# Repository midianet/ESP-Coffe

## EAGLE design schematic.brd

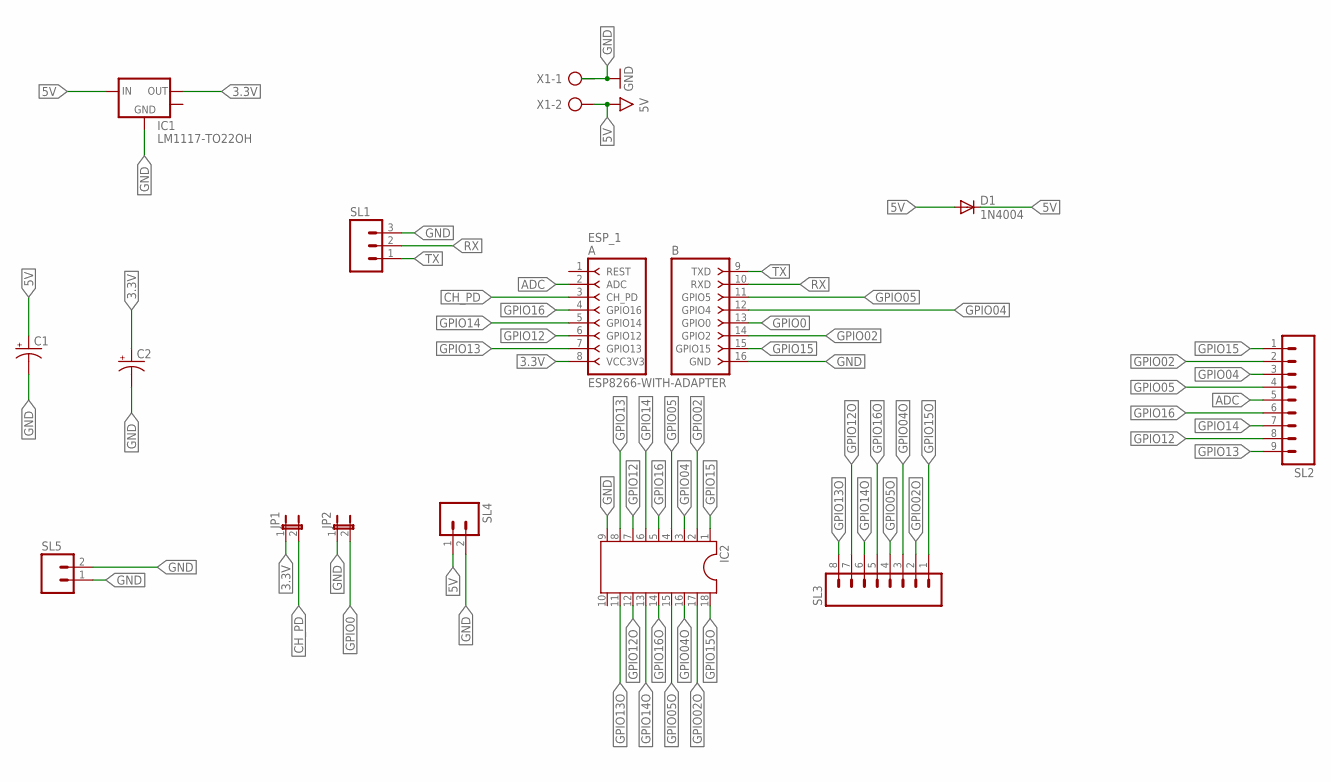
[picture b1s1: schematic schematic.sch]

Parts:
C1, C2: CPOL-USE2-4; E2-4
D1: 1N4004; DO41-10
ESP_1: ESP8266-WITH-ADAPTER; ESP8266-ADAPTER
IC1: LM1117-TO22OH; TO220L1
IC2: DIL18
JP1, JP2: JP1E; JP1
SL1: M03; 03P
SL2: M09; 09P
SL3: M08; 08P
SL4, SL5: M02; 02P
X1: AK500/2-H

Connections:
3.3V: C2.+, ESP_1.8 (VCC3V3), IC1.2 (VOUT), JP1.1
5V: C1.+, D1.A, D1.C, IC1.3 (VIN), SL4.1, X1.2
ADC: ESP_1.2 (ADC), SL2.5
CH_PD: ESP_1.3 (CH_PD), JP1.2
GND: C1.-, C2.-, ESP_1.16 (GND), IC1.1 (GND), IC2.9, JP2.1, SL1.3, SL4.2, SL5.1, SL5.2, X1.1
GPIO0: ESP_1.13 (GPIO0), JP2.2
GPIO02: ESP_1.14 (GPIO2), IC2.2, SL2.2
GPIO02O: IC2.17, SL3.2
GPIO04: ESP_1.12 (GPIO4), IC2.3, SL2.3
GPIO04O: IC2.16, SL3.3
GPIO05: ESP_1.11 (GPIO5), IC2.4, SL2.4
GPIO05O: IC2.15, SL3.4
GPIO12: ESP_1.6 (GPIO12), IC2.7, SL2.8
GPIO12O: IC2.12, SL3.7
GPIO13: ESP_1.7 (GPIO13), IC2.8, SL2.9
GPIO13O: IC2.11, SL3.8
GPIO14: ESP_1.5 (GPIO14), IC2.6, SL2.7
GPIO14O: IC2.13, SL3.6
GPIO15: ESP_1.15 (GPIO15), IC2.1, SL2.1
GPIO15O: IC2.18, SL3.1
GPIO16: ESP_1.4 (GPIO16), IC2.5, SL2.6
GPIO16O: IC2.14, SL3.5
RX: ESP_1.10 (RXD), SL1.2
TX: ESP_1.9 (TXD), SL1.1

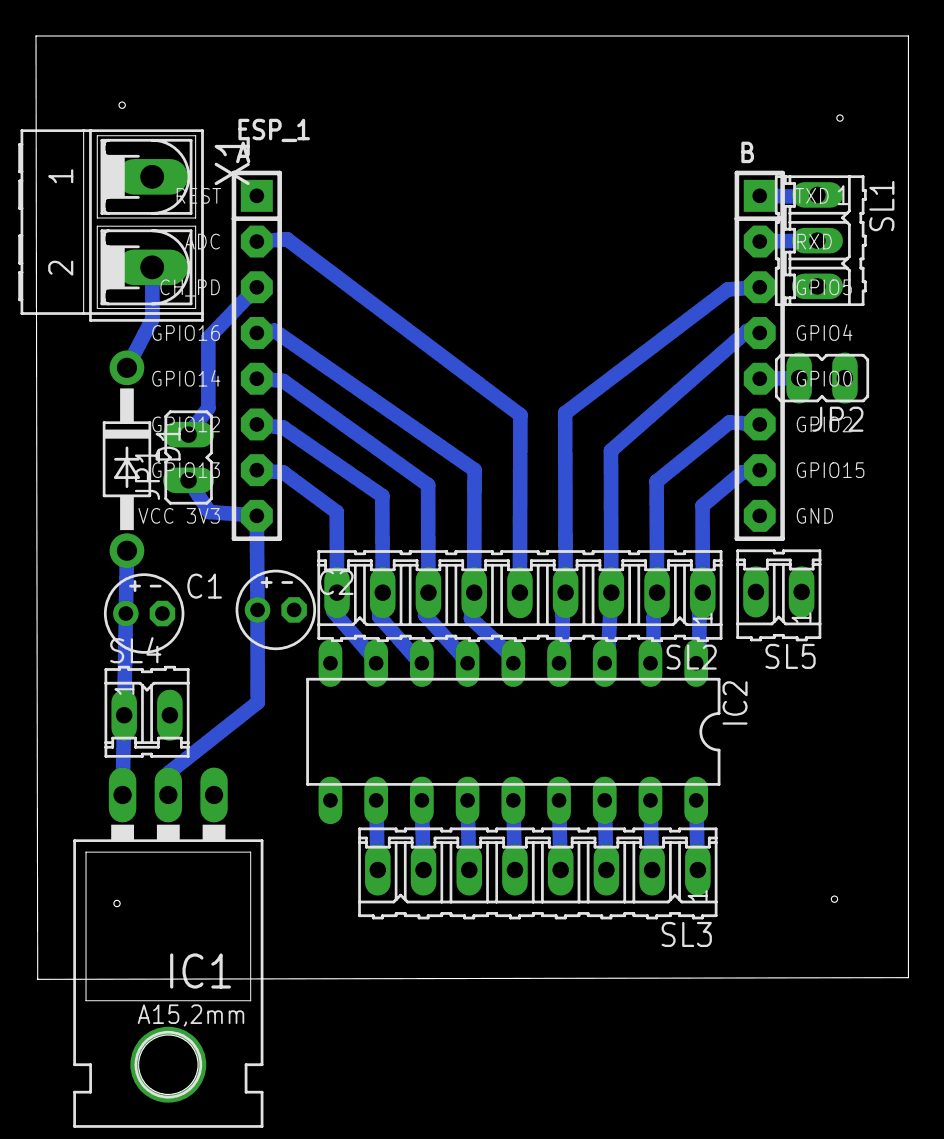
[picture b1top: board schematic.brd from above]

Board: 2 copper layers, 48.5 x 52.4 mm, 14 parts (0 on the bottom side), 24 nets.

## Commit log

2018-07-06 project esp-coffe
